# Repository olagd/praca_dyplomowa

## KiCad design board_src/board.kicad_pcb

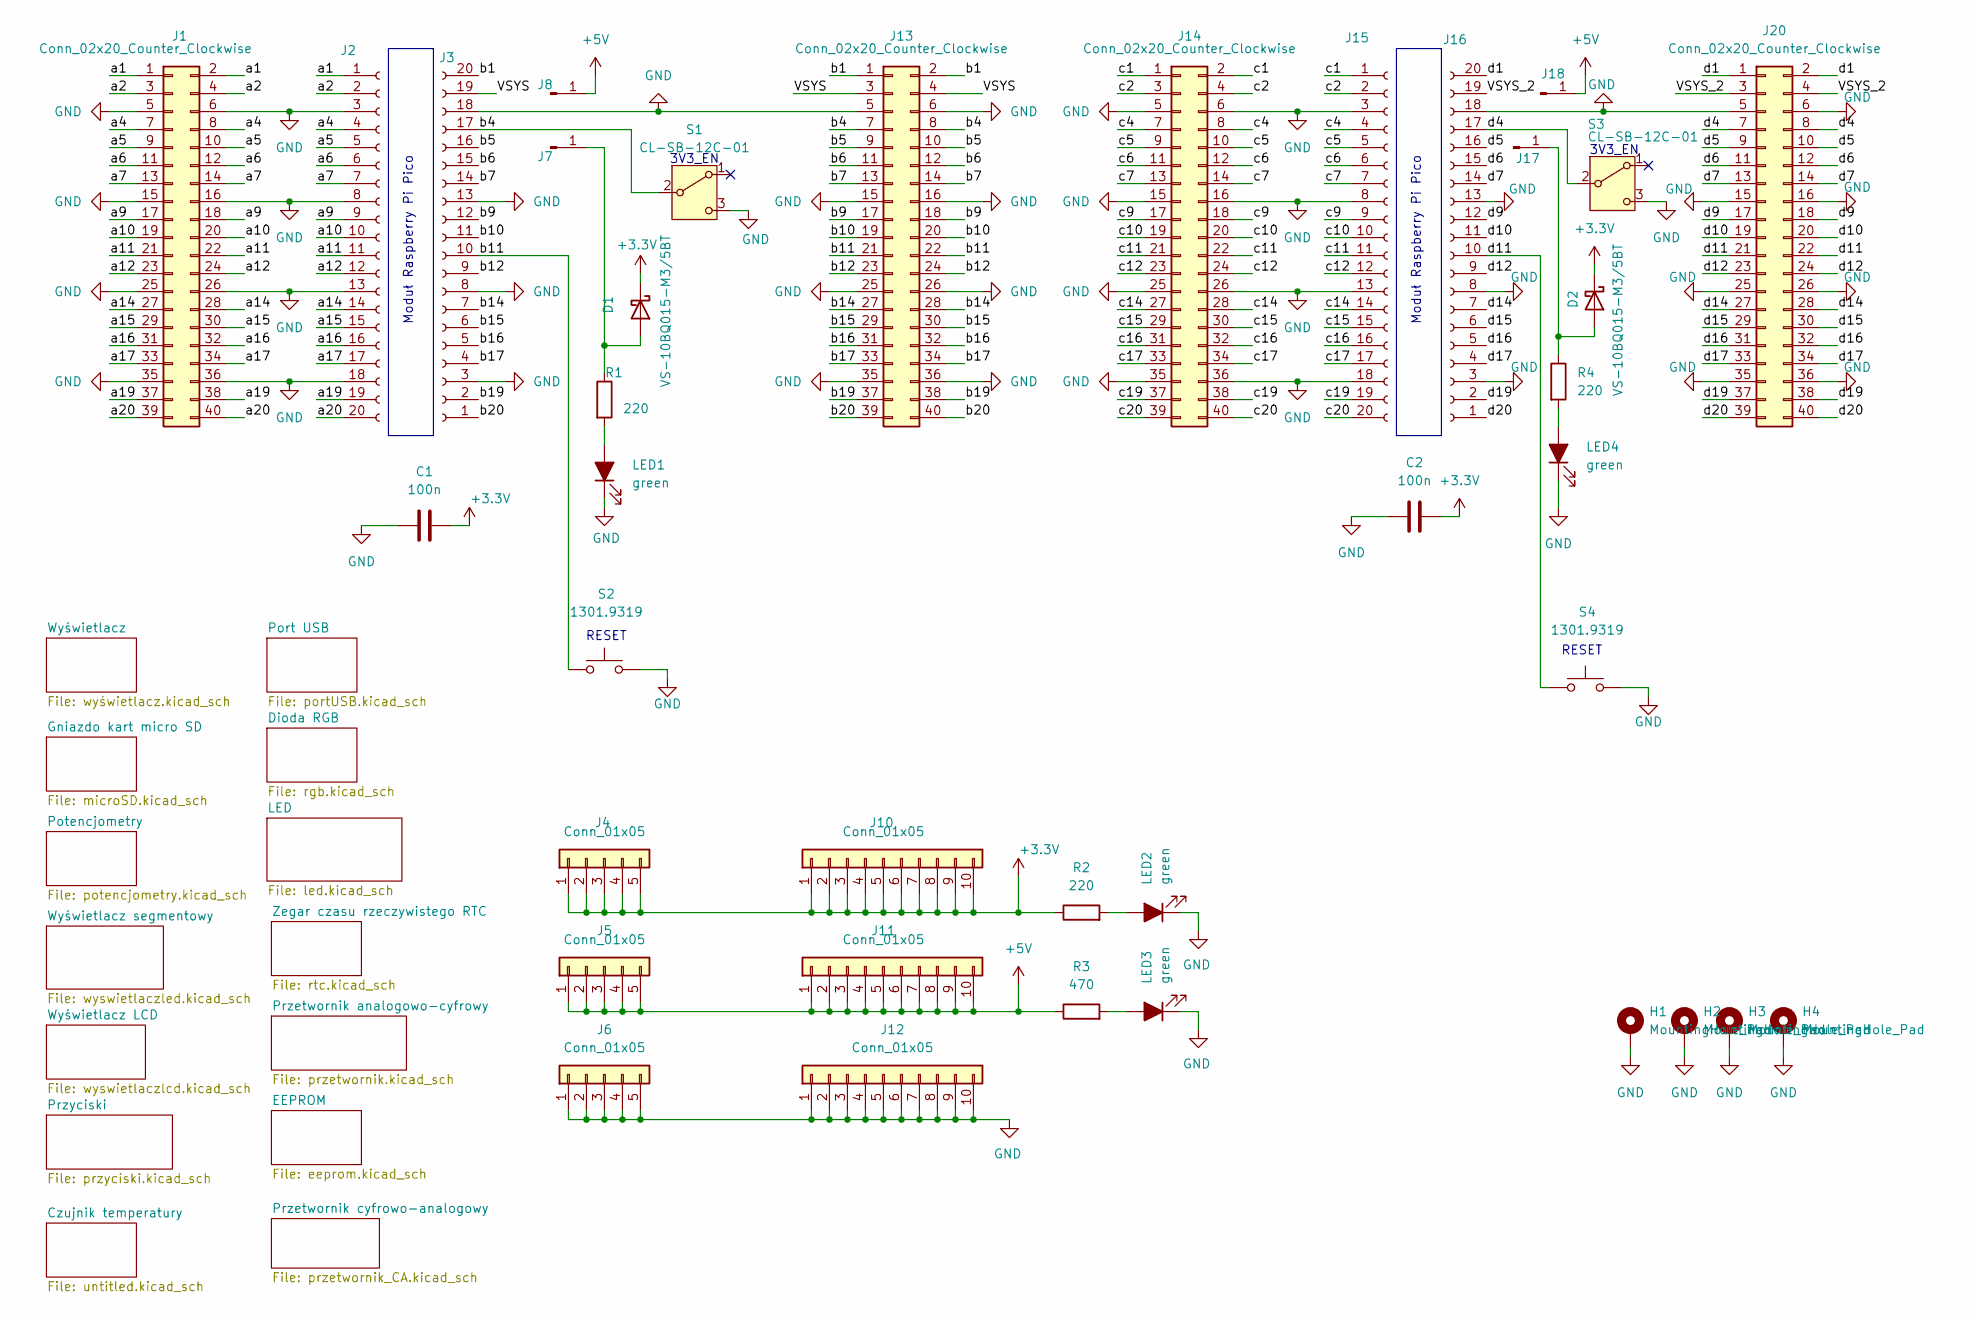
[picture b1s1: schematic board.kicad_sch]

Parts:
C1, C2: 100n; C_0603_1608Metric_Pad1.08x0.95mm_HandSolder
D1, D2: VS-10BQ015-M3/5BT; D_SMB_Handsoldering
H1, H2, H3, H4: MountingHole_Pad; MountingHole_3.2mm_M3_DIN965_Pad_TopBottom
J1, J13, J14, J20: Conn_02x20_Counter_Clockwise; PinHeader_2x20_P2.54mm_Vertical
J2, J3, J15, J16: Conn_01x20_Socket; PinSocket_1x20_P2.54mm_Vertical
J4, J5, J6, J10, J11, J12: Conn_01x05; PinHeader_1x05_P2.54mm_Vertical
J7, J8, J17, J18: Conn_01x01_Pin; PinHeader_1x01_P2.54mm_Vertical
LED1, LED2, LED3, LED4: green; LED_0603_1608Metric_Pad1.05x0.95mm_HandSolder; Manufacturer_Part_Number VLMTG1300-GS08
R1, R2, R4: 220; R_0603_1608Metric_Pad0.98x0.95mm_HandSolder
R3: 470; R_0603_1608Metric_Pad0.98x0.95mm_HandSolder
S1, S3: CL-SB-12C-01; JS102011CQN; Manufacturer_Part_Number CL-SB-12C-01
S2, S4: 1301.9319; SW_PUSH_6mm_H9.5mm; Manufacturer_Part_Number 1301.9319

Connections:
+3.3V: C1.2, C2.2, D1.1 (K), D2.1 (K), J4.1, J4.2, J4.3, J4.4, J4.5, J10.1, J10.2, J10.3, J10.4, J10.5, J10.6, J10.7, J10.8, J10.9, J10.10, R2.1; also elsewhere on the board
+5V: J5.1, J5.2, J5.3, J5.4, J5.5, J8.1, J11.1, J11.2, J11.3, J11.4, J11.5, J11.6, J11.7, J11.8, J11.9, J11.10, J18.1, R3.1; also elsewhere on the board
/VSYS: J3.19, J13.3, J13.4
/VSYS_2: J16.19, J20.3, J20.4
/a1: J1.1, J1.2, J2.1
/a2: J1.3, J1.4, J2.2
/a4: J1.7, J1.8, J2.4
/a5: J1.9, J1.10, J2.5
/a6: J1.11, J1.12, J2.6
/a7: J1.13, J1.14, J2.7
/a9: J1.17, J1.18, J2.9
/a10: J1.19, J1.20, J2.10
/a11: J1.21, J1.22, J2.11
/a12: J1.23, J1.24, J2.12
/a14: J1.27, J1.28, J2.14
/a15: J1.29, J1.30, J2.15
/a16: J1.31, J1.32, J2.16
/a17: J1.33, J1.34, J2.17
/a19: J1.37, J1.38, J2.19
/a20: J1.39, J1.40, J2.20
/b1: J3.20, J13.1, J13.2
/b4: J3.17, J13.7, J13.8, S1.2 (B)
/b5: J3.16, J13.9, J13.10
/b6: J3.15, J13.11, J13.12
/b7: J3.14, J13.13, J13.14
/b9: J3.12, J13.17, J13.18
/b10: J3.11, J13.19, J13.20
/b11: J3.10, J13.21, J13.22, S2.1
/b12: J3.9, J13.23, J13.24
/b14: J3.7, J13.27, J13.28
/b15: J3.6, J13.29, J13.30
/b16: J3.5, J13.31, J13.32
/b17: J3.4, J13.33, J13.34
/b19: J3.2, J13.37, J13.38
/b20: J3.1, J13.39, J13.40
/c1: J14.1, J14.2, J15.1
/c2: J14.3, J14.4, J15.2
/c4: J14.7, J14.8, J15.4
/c5: J14.9, J14.10, J15.5
/c6: J14.11, J14.12, J15.6
/c7: J14.13, J14.14, J15.7
/c9: J14.17, J14.18, J15.9
/c10: J14.19, J14.20, J15.10
/c11: J14.21, J14.22, J15.11
/c12: J14.23, J14.24, J15.12
/c14: J14.27, J14.28, J15.14
/c15: J14.29, J14.30, J15.15
/c16: J14.31, J14.32, J15.16
/c17: J14.33, J14.34, J15.17
/c19: J14.37, J14.38, J15.19
/c20: J14.39, J14.40, J15.20
/d1: J16.20, J20.1, J20.2
/d4: J16.17, J20.7, J20.8, S3.2 (B)
/d5: J16.16, J20.9, J20.10
/d6: J16.15, J20.11, J20.12
/d7: J16.14, J20.13, J20.14
/d9: J16.12, J20.17, J20.18
/d10: J16.11, J20.19, J20.20
/d11: J16.10, J20.21, J20.22, S4.1
/d12: J16.9, J20.23, J20.24
/d14: J16.7, J20.27, J20.28
/d15: J16.6, J20.29, J20.30
/d16: J16.5, J20.31, J20.32
/d17: J16.4, J20.33, J20.34
/d19: J16.2, J20.37, J20.38
/d20: J16.1, J20.39, J20.40
GND: C1.1, C2.1, H1.1, H2.1, H3.1, H4.1, J1.5, J1.6, J1.15, J1.16, J1.25, J1.26, J1.35, J1.36, J2.3, J2.8, J2.13, J2.18, J3.3, J3.8, J3.13, J3.18, J6.1, J6.2, J6.3, J6.4, J6.5, J12.1, J12.2, J12.3, J12.4, J12.5, J12.6, J12.7, J12.8, J12.9, J12.10, J13.5, J13.6, J13.15, J13.16, J13.25, J13.26, J13.35, J13.36, J14.5, J14.6, J14.15, J14.16, J14.25, J14.26, J14.35, J14.36, J15.3, J15.8, J15.13, J15.18, J16.3, J16.8, J16.13, J16.18, J20.5, J20.6, J20.15, J20.16, J20.25, J20.26, J20.35, J20.36, LED1.1 (K), LED2.1 (K), LED3.1 (K), LED4.1 (K), S1.3 (C), S2.2, S3.3 (C), S4.2; also elsewhere on the board
unnamed: D1.2 (A), J7.1, R1.1
unnamed: D2.2 (A), J17.1, R4.1
unnamed: LED1.2 (A), R1.2
unnamed: LED2.2 (A), R2.2
unnamed: LED3.2 (A), R3.2
unnamed: LED4.2 (A), R4.2

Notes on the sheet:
RESET
3V3_EN
Moduł Raspberry Pi Pico

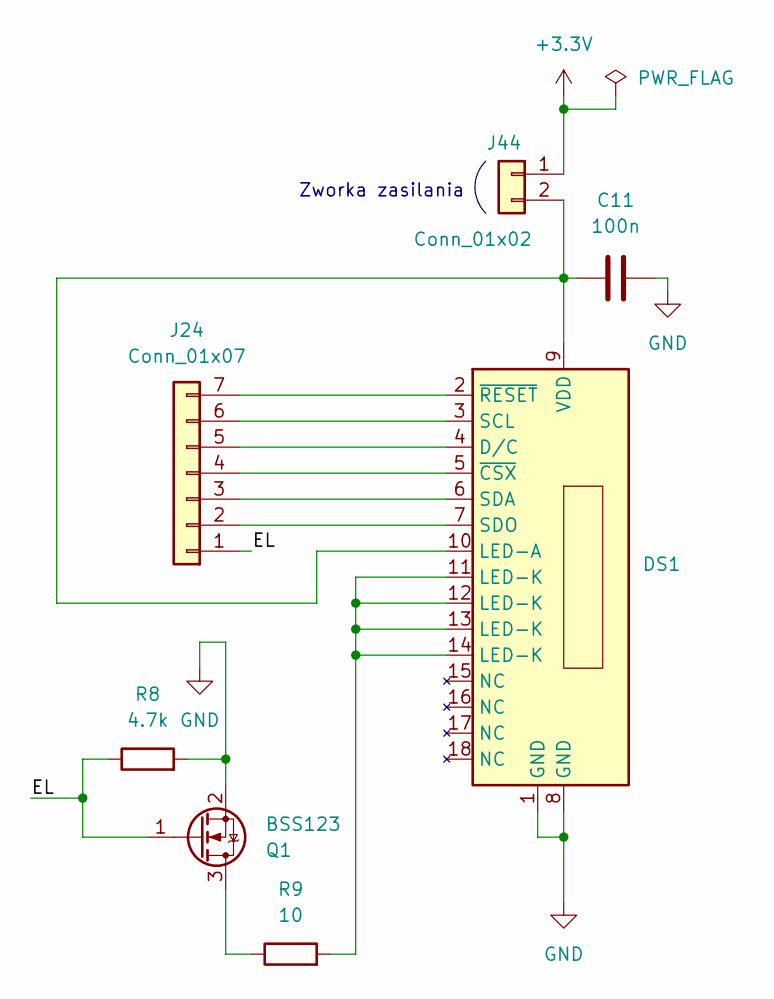
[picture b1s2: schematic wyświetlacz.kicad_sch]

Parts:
C11: 100n; C_0603_1608Metric_Pad1.08x0.95mm_HandSolder
DS1: HC28010-D; hc28010-d
J24: Conn_01x07; PinHeader_1x07_P2.54mm_Vertical
J44: Conn_01x02; PinHeader_1x02_P2.54mm_Vertical
Q1: BSS123; SOT-23_Handsoldering
R8: 4.7k; R_0603_1608Metric_Pad0.98x0.95mm_HandSolder
R9: 10; R_0603_1608Metric_Pad0.98x0.95mm_HandSolder

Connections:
+3.3V: J44.1; also elsewhere on the board
/Wyświetlacz/EL: J24.1, Q1.1 (G), R8.1
GND: C11.2, DS1.1 (GND), DS1.8 (GND), Q1.2 (S), R8.2; also elsewhere on the board
unnamed: DS1.4 (D/C), J24.5
unnamed: C11.1, DS1.9 (VDD), DS1.10 (LED-A), J44.2
unnamed: DS1.11 (LED-K), DS1.12 (LED-K), DS1.13 (LED-K), DS1.14 (LED-K), R9.2
unnamed: DS1.3 (SCL), J24.6
unnamed: DS1.6 (SDA), J24.3
unnamed: DS1.7 (SDO), J24.2
unnamed: DS1.5 (~CSX), J24.4
unnamed: DS1.2 (~RESET), J24.7
unnamed: Q1.3 (D), R9.1

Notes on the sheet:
Zworka zasilania

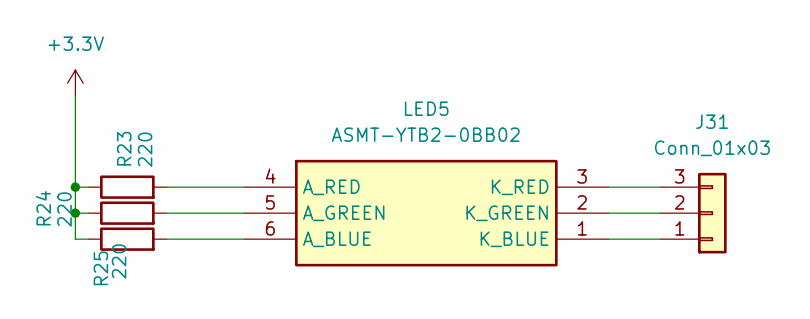
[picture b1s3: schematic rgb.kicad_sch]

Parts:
J31: Conn_01x03; PinHeader_1x03_P2.54mm_Vertical
LED5: ASMT-YTB2-0BB02; ASMT-YTC7-0AA02; Manufacturer_Part_Number ASMT-YTB2-0BB02
R23, R24, R25: 220; R_0603_1608Metric_Pad0.98x0.95mm_HandSolder

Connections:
+3.3V: R23.1, R24.1, R25.1; also elsewhere on the board
unnamed: J31.1, LED5.1 (K_BLUE)
unnamed: J31.2, LED5.2 (K_GREEN)
unnamed: J31.3, LED5.3 (K_RED)
unnamed: LED5.6 (A_BLUE), R25.2
unnamed: LED5.5 (A_GREEN), R24.2
unnamed: LED5.4 (A_RED), R23.2

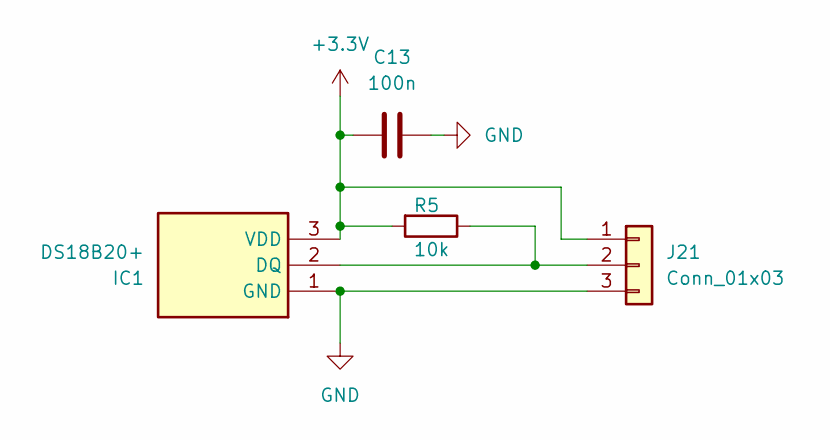
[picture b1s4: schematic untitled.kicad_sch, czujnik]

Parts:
C13: 100n; C_0603_1608Metric_Pad1.08x0.95mm_HandSolder
IC1: DS18B20+; TO-92L_Inline_Wide; Manufacturer_Part_Number DS18B20+
J21: Conn_01x03; PinHeader_1x03_P2.54mm_Vertical
R5: 10k; R_0603_1608Metric_Pad0.98x0.95mm_HandSolder

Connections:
+3.3V: C13.1, IC1.3 (VDD), J21.1, R5.2; also elsewhere on the board
GND: C13.2, IC1.1 (GND), J21.3; also elsewhere on the board
unnamed: IC1.2 (DQ), J21.2, R5.1

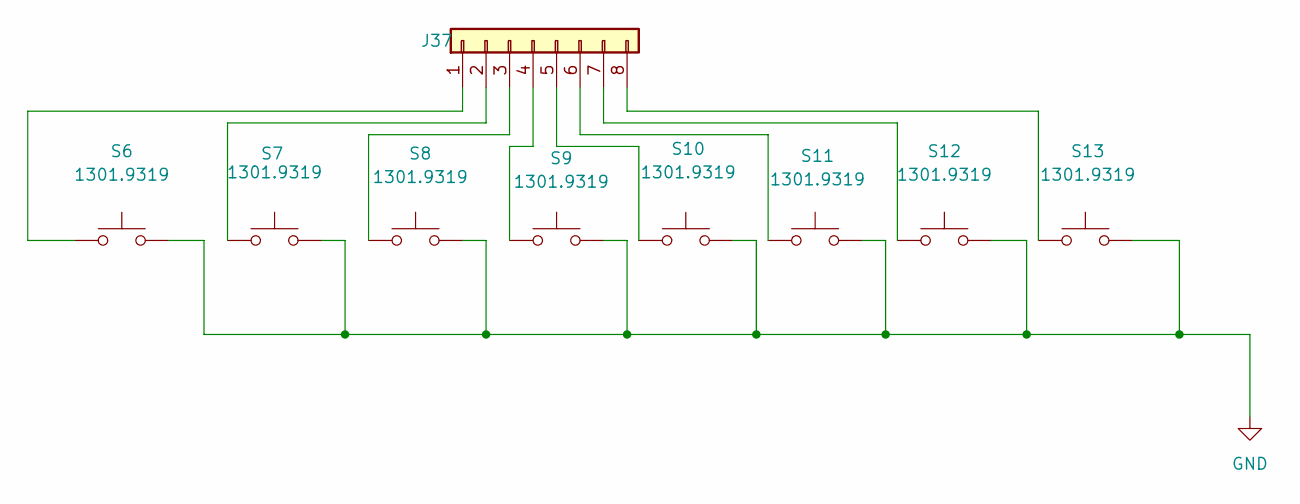
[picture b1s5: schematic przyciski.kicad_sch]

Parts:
J37: Conn_01x08; PinHeader_1x08_P2.54mm_Vertical
S6, S7, S8, S9, S10, S11, S12, S13: 1301.9319; SW_PUSH_6mm_H9.5mm; Manufacturer_Part_Number 1301.9319

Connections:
GND: S6.2, S7.2, S8.2, S9.2, S10.2, S11.2, S12.2, S13.2; also elsewhere on the board
unnamed: J37.1, S6.1
unnamed: J37.2, S7.1
unnamed: J37.3, S8.1
unnamed: J37.4, S9.1
unnamed: J37.5, S10.1
unnamed: J37.6, S11.1
unnamed: J37.7, S12.1
unnamed: J37.8, S13.1

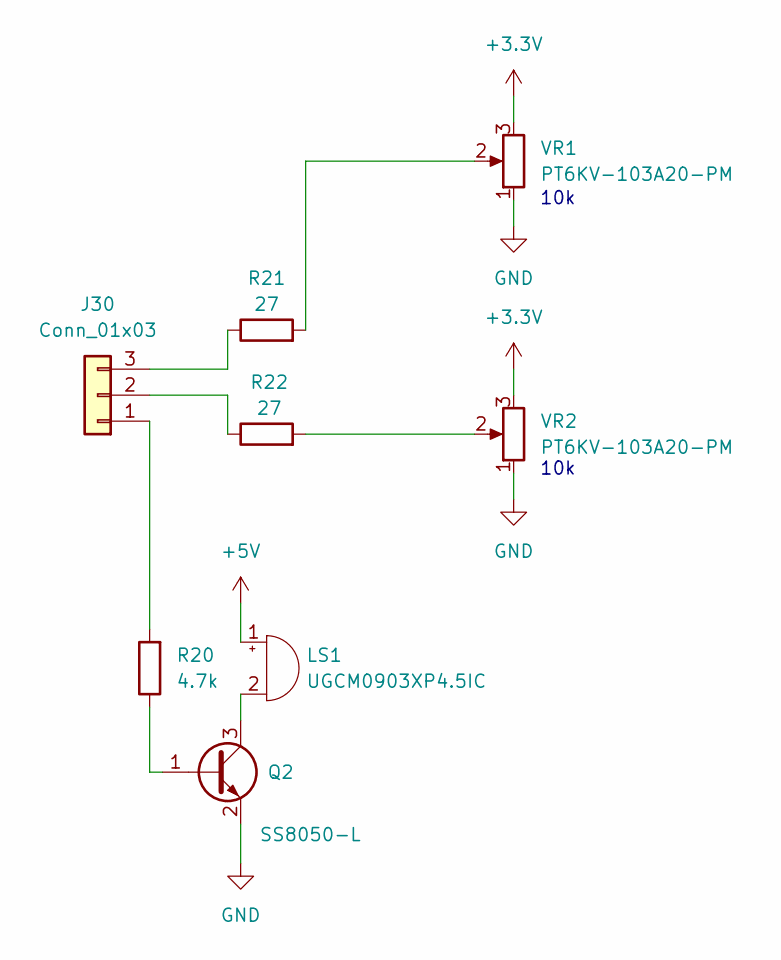
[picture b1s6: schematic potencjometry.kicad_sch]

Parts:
J30: Conn_01x03; PinHeader_1x03_P2.54mm_Vertical
LS1: UGCM0903XP4.5IC; BMT0905XH05; Manufacturer_Part_Number BMT0905XH05
Q2: SS8050-L; SOT-23_Handsoldering
R20: 4.7k; R_0603_1608Metric_Pad0.98x0.95mm_HandSolder
R21, R22: 27; R_0603_1608Metric_Pad0.98x0.95mm_HandSolder
VR1, VR2: PT6KV-103A20-PM; PT6KV251A2020; Mouser Part Number 531-PT6KV-251A2020

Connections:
+3.3V: VR1.3, VR2.3; also elsewhere on the board
+5V: LS1.1 (+); also elsewhere on the board
GND: Q2.2 (E), VR1.1, VR2.1; also elsewhere on the board
unnamed: J30.1, R20.2
unnamed: J30.2, R22.1
unnamed: J30.3, R21.1
unnamed: LS1.2 (-), Q2.3 (C)
unnamed: Q2.1 (B), R20.1
unnamed: R21.2, VR1.2
unnamed: R22.2, VR2.2

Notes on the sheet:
10k

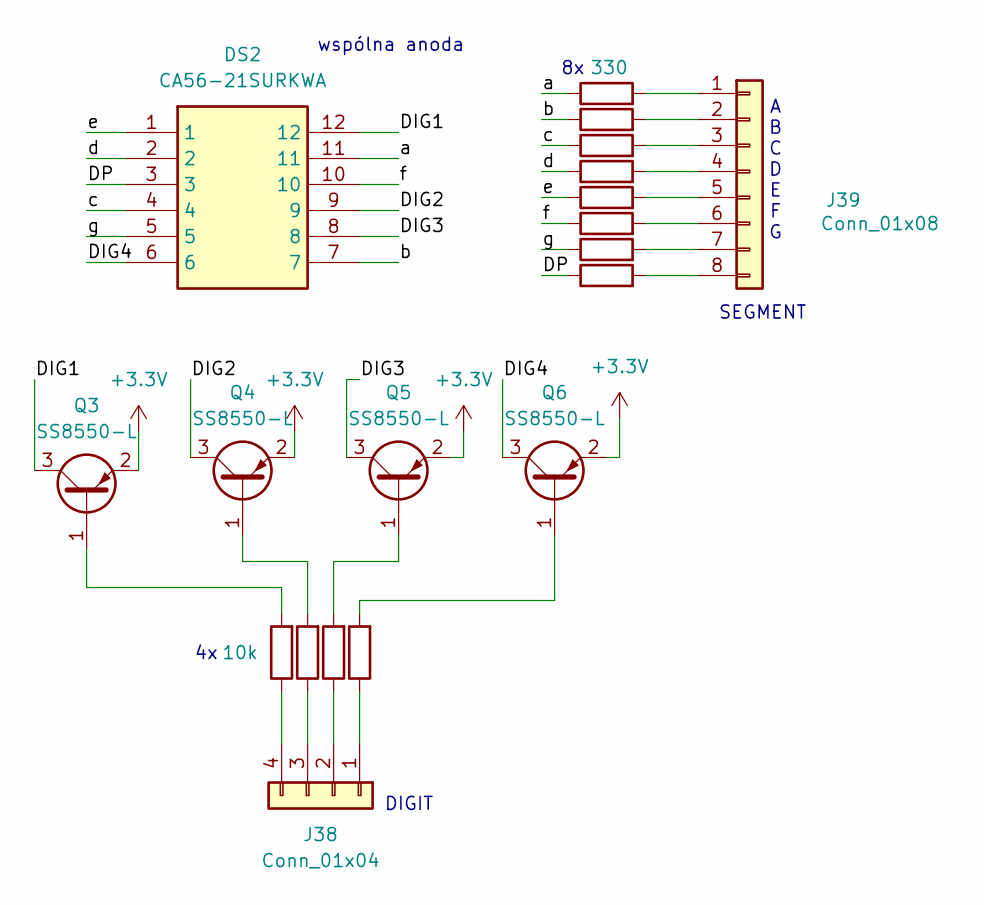
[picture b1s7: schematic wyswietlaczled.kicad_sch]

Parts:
DS2: CA56-21SURKWA; wyswietlacz7x4; Manufacturer_Part_Number CA56-21SURKWA
J38: Conn_01x04; PinHeader_1x04_P2.54mm_Vertical
J39: Conn_01x08; PinHeader_1x08_P2.54mm_Vertical
Q3, Q4, Q5, Q6: SS8550-L; SOT-23_Handsoldering
R39, R40, R41, R42: 10k; R_0603_1608Metric_Pad0.98x0.95mm_HandSolder
R43, R45, R46, R47, R48, R49, R50: 330; R_0603_1608Metric_Pad0.98x0.95mm_HandSolder
R44: 220; R_0603_1608Metric_Pad0.98x0.95mm_HandSolder

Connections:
+3.3V: Q3.2 (E), Q4.2 (E), Q5.2 (E), Q6.2 (E); also elsewhere on the board
/Wyświetlacz segmentowy/DIG1: DS2.12, Q3.3 (C)
/Wyświetlacz segmentowy/DIG2: DS2.9, Q4.3 (C)
/Wyświetlacz segmentowy/DIG3: DS2.8, Q5.3 (C)
/Wyświetlacz segmentowy/DIG4: DS2.6, Q6.3 (C)
/Wyświetlacz segmentowy/DP: DS2.3, R50.1
/Wyświetlacz segmentowy/a: DS2.11, R43.1
/Wyświetlacz segmentowy/b: DS2.7, R44.1
/Wyświetlacz segmentowy/c: DS2.4, R45.1
/Wyświetlacz segmentowy/d: DS2.2, R46.1
/Wyświetlacz segmentowy/e: DS2.1, R47.1
/Wyświetlacz segmentowy/f: DS2.10, R48.1
/Wyświetlacz segmentowy/g: DS2.5, R49.1
unnamed: J38.1, R42.1
unnamed: J38.2, R41.1
unnamed: J38.3, R40.1
unnamed: J38.4, R39.1
unnamed: J39.1, R43.2
unnamed: J39.2, R44.2
unnamed: J39.3, R45.2
unnamed: J39.4, R46.2
unnamed: J39.5, R47.2
unnamed: J39.6, R48.2
unnamed: J39.7, R49.2
unnamed: J39.8, R50.2
unnamed: Q3.1 (B), R39.2
unnamed: Q4.1 (B), R40.2
unnamed: Q5.1 (B), R41.2
unnamed: Q6.1 (B), R42.2

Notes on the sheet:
DIGIT
A B C D E F G
SEGMENT
wspólna anoda

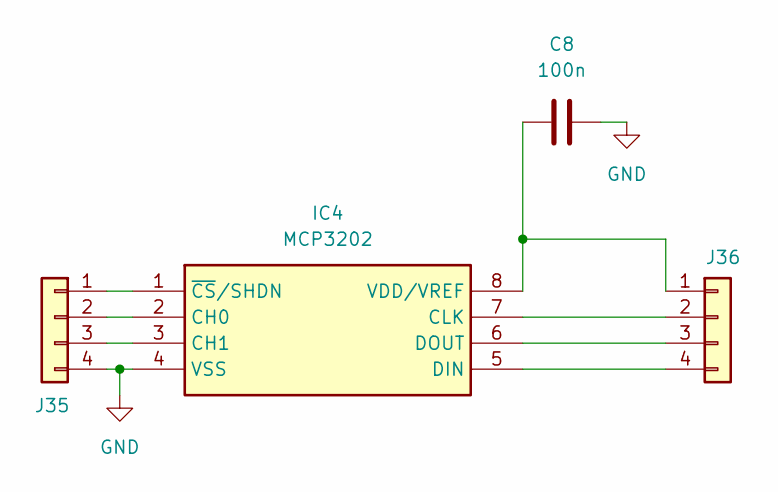
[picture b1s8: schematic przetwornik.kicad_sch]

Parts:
C8: 100n; C_0603_1608Metric_Pad1.08x0.95mm_HandSolder
IC4: MCP3202; DIP-8_W7.62mm_Socket_LongPads; Mouser Part Number 579-MCP3202-CI/MS
J35, J36: Conn_01x04; PinHeader_1x04_P2.54mm_Vertical

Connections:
GND: C8.2, IC4.4 (VSS), J35.4; also elsewhere on the board
unnamed: IC4.2 (CH0), J35.2
unnamed: IC4.3 (CH1), J35.3
unnamed: IC4.7 (CLK), J36.2
unnamed: IC4.5 (DIN), J36.4
unnamed: IC4.6 (DOUT), J36.3
unnamed: C8.1, IC4.8 (VDD/VREF), J36.1
unnamed: IC4.1 (~CS/SHDN), J35.1

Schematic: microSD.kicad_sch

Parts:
C6: 100n; C_0603_1608Metric_Pad1.08x0.95mm_HandSolder
J28: Conn_01x07; PinHeader_1x07_P2.54mm_Vertical
J29: 112J-TDAR-R01; 112JTDARR01; Manufacturer_Part_Number 112J-TDAR-R01
R13, R14, R15, R16, R17, R18, R19: 47k; R_0603_1608Metric_Pad0.98x0.95mm_HandSolder

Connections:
+3.3V: C6.2, J29.4 (VDD), R13.2, R14.2, R15.2, R16.2, R17.2, R18.2, R19.2; also elsewhere on the board
/Gniazdo kart micro SD/m1: J28.1, J29.1 (DAT2), R13.1
/Gniazdo kart micro SD/m2: J28.2, J29.2 (CD/DAT3), R14.1
/Gniazdo kart micro SD/m3: J28.3, J29.3 (CMD), R15.1
/Gniazdo kart micro SD/m4: J28.4, J29.5 (CLK), R16.1
/Gniazdo kart micro SD/m5: J28.5, J29.7 (DAT0), R17.1
/Gniazdo kart micro SD/m6: J28.6, J29.8 (DAT1), R18.1
/Gniazdo kart micro SD/m7: J28.7, J29.CD1 (CARD_DETECTION), R19.1
GND: C6.1, J29.6 (VSS), J29.G1 (GROUND), J29.MP1, J29.MP2, J29.MP3; also elsewhere on the board

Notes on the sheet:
7 x 47k rezystory podciągające

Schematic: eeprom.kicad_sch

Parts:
C3: 100n; C_0603_1608Metric_Pad1.08x0.95mm_HandSolder
IC2: M24C02-WMN6TP; SOIC-8_3.9x4.9mm_P1.27mm; Manufacturer_Part_Number M24C02-WMN6TP
J22, J23: Conn_01x02_Pin; PinHeader_1x02_P2.54mm_Vertical
R6, R7: 10k; R_0603_1608Metric_Pad0.98x0.95mm_HandSolder

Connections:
+3.3V: C3.1, IC2.8 (VCC), R6.2, R7.2; also elsewhere on the board
GND: C3.2, IC2.1 (E0), IC2.2 (E1), IC2.3 (E2), IC2.4 (VSS), IC2.7 (~WC), J22.1, J22.2; also elsewhere on the board
unnamed: IC2.6 (SCL), J23.2, R7.1
unnamed: IC2.5 (SDA), J23.1, R6.1

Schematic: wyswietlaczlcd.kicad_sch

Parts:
H5, H6, H7, H8: MountingHole; MountingHole_2.7mm_M2.5
J40: Conn_01x16_Socket; PinSocket_1x16_P2.54mm_Vertical
J41: Conn_02x07_Odd_Even; PinHeader_2x07_P2.54mm_Vertical
Q7: SS8050-L; SOT-23_Handsoldering
R51: 4.7k; R_0603_1608Metric_Pad0.98x0.95mm_HandSolder
R52: 50; R_0603_1608Metric_Pad0.98x0.95mm_HandSolder
RV1: 10K; PT6KV251A2020

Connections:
+3.3V: J41.4; also elsewhere on the board
+5V: J40.2, R52.1, RV1.1; also elsewhere on the board
/Wyświetlacz LCD/BL: J41.6, R51.1
/Wyświetlacz LCD/D0: J40.7, J41.8
/Wyświetlacz LCD/D1: J40.8, J41.10
/Wyświetlacz LCD/D2: J40.9, J41.12
/Wyświetlacz LCD/D3: J40.10, J41.14
/Wyświetlacz LCD/D4: J40.11, J41.7
/Wyświetlacz LCD/D5: J40.12, J41.9
/Wyświetlacz LCD/D6: J40.13, J41.11
/Wyświetlacz LCD/D7: J40.14, J41.13
/Wyświetlacz LCD/E: J40.6, J41.5
/Wyświetlacz LCD/RS: J40.4, J41.3
GND: J40.1, J40.5, J41.1, J41.2, Q7.2 (E), RV1.3; also elsewhere on the board
unnamed: J40.3, RV1.2
unnamed: J40.15, R52.2
unnamed: J40.16, Q7.3 (C)
unnamed: Q7.1 (B), R51.2

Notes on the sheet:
Dla bezpieczeństwa połączony z masą, by porty wyświetlacza były zawsze wejściowe i napięcie +5V nie pojawiło się na pinach GPIO Raspberry Pi Pico
R/W

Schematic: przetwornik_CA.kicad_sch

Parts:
C9, C10: 100n; C_0603_1608Metric_Pad1.08x0.95mm_HandSolder
IC5: MCP4921-E_P; DIP-8_W7.62mm_Socket_LongPads; Mouser Part Number 579-MCP4921-E/P
J42, J43: Conn_01x04; PinHeader_1x04_P2.54mm_Vertical

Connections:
GND: C9.2, C10.2, IC5.7 (VSS), J43.2; also elsewhere on the board
unnamed: IC5.3 (SCK), J42.3
unnamed: IC5.4 (SDI), J42.4
unnamed: C9.1, IC5.1 (VDD), J42.1
unnamed: IC5.8 (VOUT), J43.1
unnamed: C10.1, IC5.6 (VREF), J43.3
unnamed: IC5.2 (~CS), J42.2
unnamed: IC5.5 (~LDAC), J43.4

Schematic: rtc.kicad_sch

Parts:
C4: 10p; C_0603_1608Metric_Pad1.08x0.95mm_HandSolder
C5: 100n; C_0603_1608Metric_Pad1.08x0.95mm_HandSolder
D3, D4: VS-10BQ015-M3/5BT; D_SMB_Handsoldering
J25, J26: Conn_01x02_Pin; PinHeader_1x02_P2.54mm_Vertical
J27: Battery; PinHeader_1x02_P2.54mm_Vertical
R10: 47k; R_0603_1608Metric_Pad0.98x0.95mm_HandSolder
R11, R12: 10k; R_0603_1608Metric_Pad0.98x0.95mm_HandSolder
U1: PCF8563TS; TSSOP-8_3x3mm_P0.65mm
Y1: 32.768kHz; Crystal_AT310_D3.0mm_L10.0mm_Horizontal

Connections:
+3.3V: D4.2 (A), R10.1, R11.2, R12.2; also elsewhere on the board
/Zegar czasu rzeczywistego RTC/CLKOUT: J25.1, U1.7 (CLKO)
/Zegar czasu rzeczywistego RTC/INT: J25.2, R10.2, U1.3 (~INT)
GND: C4.1, C5.2, J27.1, U1.4 (VSS); also elsewhere on the board
unnamed: D3.2 (A), J27.2
unnamed: C5.1, D3.1 (K), D4.1 (K), U1.8 (VDD)
unnamed: J26.1, J26.3, R11.1, U1.6 (SCL)
unnamed: J26.2, J26.4, R12.1, U1.5 (SDA)
unnamed: C4.2, U1.1 (OSCI), Y1.1
unnamed: U1.2 (OSCO), Y1.2

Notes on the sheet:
Kondensator opcjonalny
Opcjonalna bateria podtrzymująca (1.5 .. 5) V
BAT+
BAT-

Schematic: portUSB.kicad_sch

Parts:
C7, C12: 100n; C_0603_1608Metric_Pad1.08x0.95mm_HandSolder
D5: VS-10BQ015-M3/5BT; D_SMB_Handsoldering
IC3: FT232RNL-TUBE; SOP65P780X200-28N; Manufacturer_Part_Number FT232RNL-TUBE
J32: Conn_02x05_Odd_Even; PinHeader_2x05_P2.54mm_Vertical
J33: USB_C_Receptacle_USB2.0_16P; USB_C_Receptacle_HRO_TYPE-C-31-M-12
LED6, LED8: green; LED_0603_1608Metric_Pad1.05x0.95mm_HandSolder; Manufacturer_Part_Number VLMTG1300-GS08
LED7: red; LED_0603_1608Metric_Pad1.05x0.95mm_HandSolder; Manufacturer_Part_Number LS Q976-NR-1
R26: 330; R_0603_1608Metric_Pad0.98x0.95mm_HandSolder
R27, R28: 5.1k; R_0603_1608Metric_Pad0.98x0.95mm_HandSolder
R29, R30: 220; R_0603_1608Metric_Pad0.98x0.95mm_HandSolder
S5: CL-SB-12C-01; JS102011CQN; Manufacturer_Part_Number CL-SB-12C-01

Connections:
+5V: C12.2, D5.1 (K), IC3.20 (VCC); also elsewhere on the board
/Port USB/3V3OUT: C7.1, IC3.4 (VCCIO), IC3.17 (3V3OUT), R29.1, R30.1
/Port USB/CB3: IC3.14 (CBUS3), J32.1
/Port USB/CB4: IC3.12 (CBUS4), J32.2
/Port USB/CTS: IC3.11 (CTS#), J32.3
/Port USB/DCD: IC3.10 (DCD#), J32.4
/Port USB/DSR: IC3.9 (DSR#), J32.5
/Port USB/DTR: IC3.2 (DTR#), J32.9
/Port USB/RI: IC3.6 (RI#), J32.6
/Port USB/RTS: IC3.3 (RTS#), J32.8
/Port USB/RXD: IC3.5 (RXD), J32.7
/Port USB/TXD: IC3.1 (TXD), J32.10
/Port USB/USBD+: IC3.15 (USBDP), J33.A6 (D+), J33.B6 (D+)
/Port USB/USBD-: IC3.16 (USBDM), J33.A7 (D-), J33.B7 (D-)
GND: C7.2, C12.1, IC3.7 (GND_1), IC3.18 (GND_2), IC3.21 (GND_3), IC3.25 (AGND), IC3.26 (TEST), J33.A1 (GND), J33.A12 (GND), J33.B1 (GND), J33.B12 (GND), J33.S1 (SHIELD), LED6.1 (K), R27.1, R28.1; also elsewhere on the board
unnamed: D5.2 (A), R26.1, S5.3 (C)
unnamed: IC3.23 (CBUS0), LED7.1 (K)
unnamed: IC3.22 (CBUS1), LED8.1 (K)
unnamed: J33.A5 (CC1), R28.2
unnamed: J33.B5 (CC2), R27.2
unnamed: LED6.2 (A), R26.2
unnamed: LED7.2 (A), R29.2
unnamed: LED8.2 (A), R30.2
unnamed: J33.A4 (VBUS), J33.A9 (VBUS), J33.B4 (VBUS), J33.B9 (VBUS), S5.2 (B)

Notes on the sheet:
+5V (VSYS)

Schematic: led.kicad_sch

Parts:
J34: Conn_01x08; PinHeader_1x08_P2.54mm_Vertical
LED9, LED11, LED13, LED15: red; LED_0603_1608Metric_Pad1.05x0.95mm_HandSolder; Manufacturer_Part_Number LS Q976-NR-1
LED10, LED12, LED14, LED16: green; LED_0603_1608Metric_Pad1.05x0.95mm_HandSolder; Manufacturer_Part_Number VLMTG1300-GS08
R31, R32, R33, R34, R35, R36, R37, R38: 220; R_0603_1608Metric_Pad0.98x0.95mm_HandSolder

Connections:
+3.3V: R31.1, R32.1, R33.1, R34.1, R35.1, R36.1, R37.1, R38.1; also elsewhere on the board
unnamed: J34.1, LED16.1 (K)
unnamed: J34.2, LED15.1 (K)
unnamed: J34.3, LED14.1 (K)
unnamed: J34.4, LED13.1 (K)
unnamed: J34.5, LED12.1 (K)
unnamed: J34.6, LED11.1 (K)
unnamed: J34.7, LED10.1 (K)
unnamed: J34.8, LED9.1 (K)
unnamed: LED9.2 (A), R31.2
unnamed: LED10.2 (A), R32.2
unnamed: LED11.2 (A), R33.2
unnamed: LED12.2 (A), R34.2
unnamed: LED13.2 (A), R35.2
unnamed: LED14.2 (A), R36.2
unnamed: LED15.2 (A), R37.2
unnamed: LED16.2 (A), R38.2

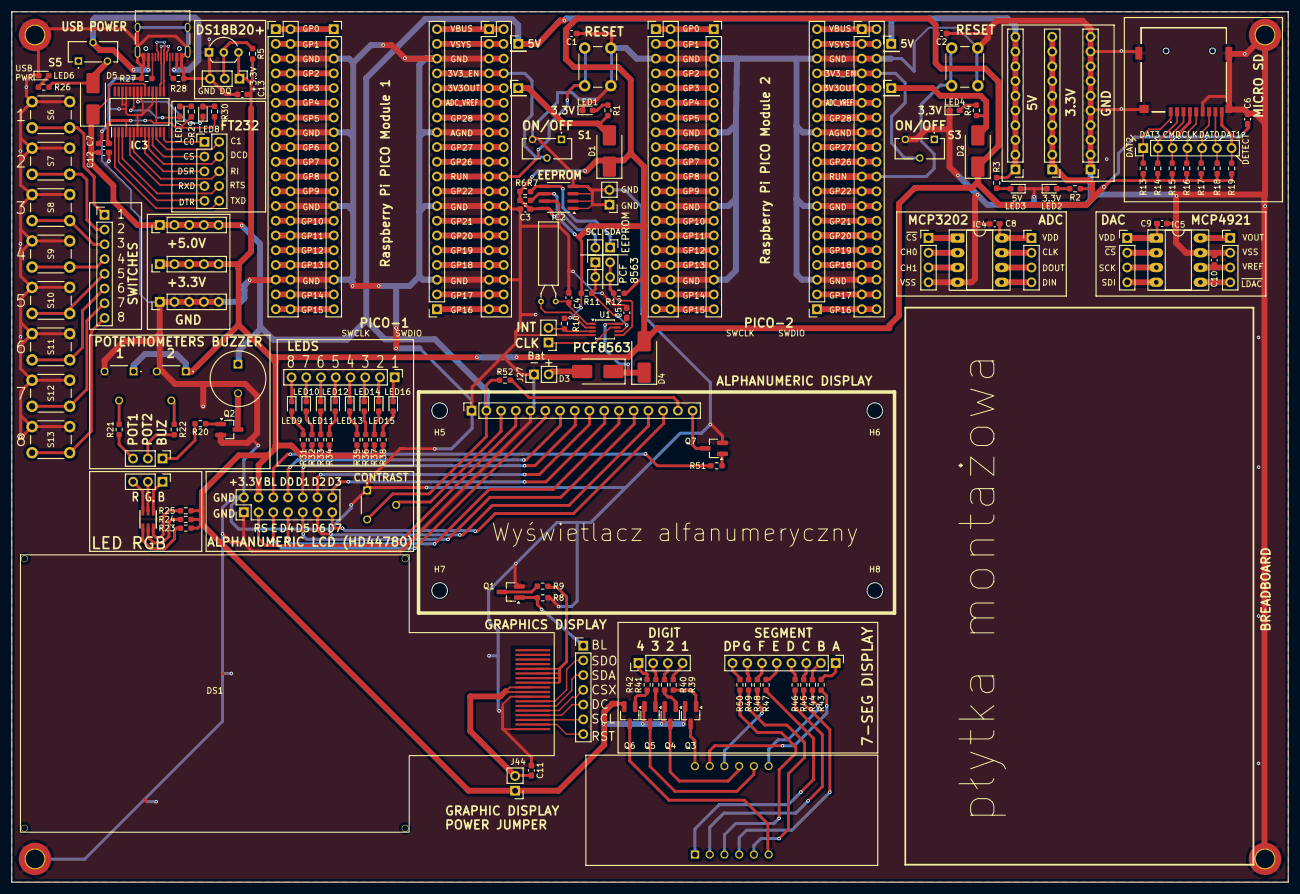
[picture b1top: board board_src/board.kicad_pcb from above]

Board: 2 copper layers, 220.0 x 150.0 mm, 169 parts (0 on the bottom side), 217 nets.

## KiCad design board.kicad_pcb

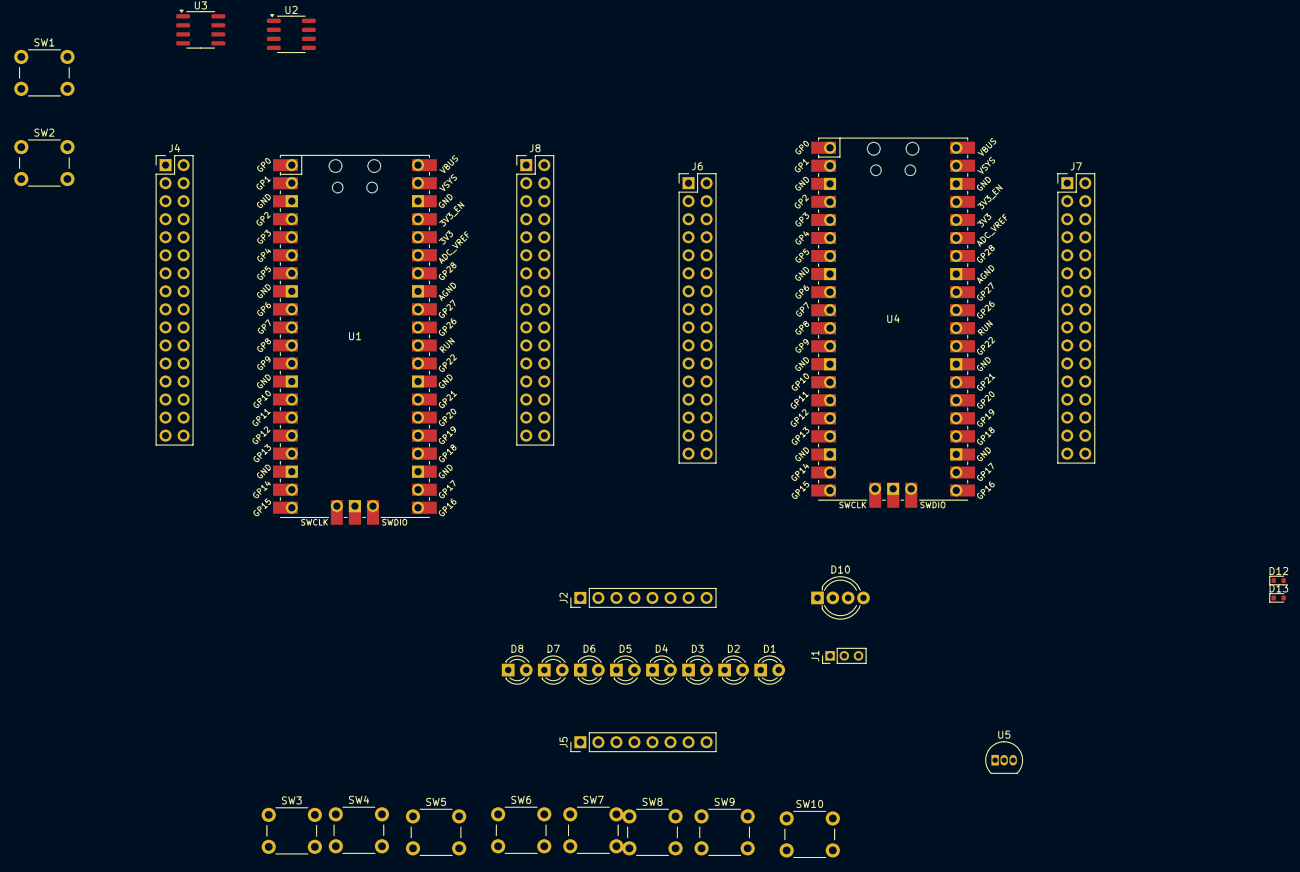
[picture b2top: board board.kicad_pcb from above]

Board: 2 copper layers, 33 parts (0 on the bottom side), 83 nets, no tracks yet.

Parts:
D1, D3, D5, D7: red; LED_D3.0mm_FlatTop
D2, D4, D6, D8: green; LED_D3.0mm_FlatTop
D10: LED; LED_D5.0mm-4_RGB_Wide_Pins
D12, D13: 1N4148WT; D_SOD-523
J1: Conn_01x03; PinHeader_1x03_P2.00mm_Vertical
J2, J5: Conn_01x08; PinHeader_1x08_P2.54mm_Vertical
J4, J6, J7, J8: Conn_02x16_Odd_Even; PinHeader_2x16_P2.54mm_Vertical
SW1, SW2: SW_Push; SW_PUSH_6mm
SW3, SW4, SW5, SW6, SW7, SW8, SW9, SW10: SW_PUSH_6mm
U1, U4: Pico; RPi_Pico_SMD_TH
U2: AT24CS04-SSHM; SOIC-8_3.9x4.9mm_P1.27mm
U3: PCF8563T; SOIC-8_3.9x4.9mm_P1.27mm
U5: DS18B20; TO-92_Inline

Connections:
+3.3V: D10.2 (A), U1.36 (3V3), U2.2 (A1), U2.8 (VCC), U3.8 (VDD), U4.36 (3V3), U5.3 (V_{DD})
/a1: J6.1, J6.2, U4.1 (GPIO0)
/a2: J6.3, J6.4, U4.2 (GPIO1)
/a3: J6.5, J6.6, U4.4 (GPIO2)
/a4: J6.7, J6.8, U4.5 (GPIO3)
/a5: J6.9, J6.10, U4.6 (GPIO4)
/a6: J6.11, J6.12, U4.7 (GPIO5)
/a7: J6.13, J6.14, U4.9 (GPIO6)
/a8: J6.15, J6.16, U4.10 (GPIO7)
/a9: J6.17, J6.18, U4.11 (GPIO8)
/a10: J6.19, J6.20, U4.12 (GPIO9)
/a11: J6.21, J6.22, U4.14 (GPIO10)
/a12: J6.23, J6.24, U4.15 (GPIO11)
/a13: J6.25, J6.26, U4.16 (GPIO12)
/a14: J6.27, J6.28, U4.17 (GPIO13)
/a15: J6.29, J6.30, U4.19 (GPIO14)
/a16: J6.31, J6.32, U4.20 (GPIO15)
/b1: J7.1, J7.2, U4.40 (VBUS)
/b2: J7.3, J7.4, U4.39 (VSYS)
/b3: J7.5, J7.6, U4.37 (3V3_EN)
/b4: J7.7, J7.8, U4.35 (ADC_VREF)
/b5: J7.9, J7.10, U4.34 (GPIO28_ADC2)
/b6: J7.11, J7.12, U4.33 (AGND)
/b7: J7.13, J7.14, J7.17, U4.32 (GPIO27_ADC1)
/b8: J7.15, J7.16, U4.31 (GPIO26_ADC0)
/b9: J7.18, U4.29 (GPIO22)
/b10: J7.19, J7.20, U4.27 (GPIO21)
/b11: J7.21, J7.22, U4.26 (GPIO20)
/b12: J7.23, J7.24, U4.25 (GPIO19)
/b13: J7.25, J7.26, U4.24 (GPIO18)
/b14: J7.27, J7.28, U4.22 (GPIO17)
/b15: J7.29, J7.30, U4.21 (GPIO16)
/c1: J4.1, J4.2, U1.1 (GPIO0)
/c2: J4.3, J4.4, U1.2 (GPIO1)
/c3: J4.5, J4.6, U1.4 (GPIO2)
/c4: J4.7, J4.8, U1.5 (GPIO3)
/c5: J4.9, J4.10, U1.6 (GPIO4)
/c6: J4.11, J4.12, U1.7 (GPIO5)
/c7: J4.13, J4.14, U1.9 (GPIO6)
/c8: J4.15, J4.16, U1.10 (GPIO7)
/c9: J4.17, J4.18, U1.11 (GPIO8)
/c10: J4.19, J4.20, U1.12 (GPIO9)
/c11: J4.21, J4.22, U1.14 (GPIO10)
/c12: J4.23, J4.24, U1.15 (GPIO11)
/c13: J4.25, J4.26, U1.16 (GPIO12)
/c14: J4.27, J4.28, U1.17 (GPIO13)
/c15: J4.29, J4.30, U1.19 (GPIO14)
/c16: J4.31, J4.32, U1.20 (GPIO15)
/d1: J8.1, J8.2, U1.40 (VBUS)
/d2: J8.3, J8.4, U1.39 (VSYS)
/d3: J8.5, J8.6, U1.37 (3V3_EN)
/d4: J8.7, J8.8, U1.35 (ADC_VREF)
/d5: J8.9, J8.10, U1.34 (GPIO28_ADC2)
/d6: J8.11, J8.12, U1.33 (AGND)
/d7: J8.13, J8.14, U1.32 (GPIO27_ADC1)
/d8: J8.15, J8.16, U1.31 (GPIO26_ADC0)
/d9: J8.17, J8.18, U1.29 (GPIO22)
/d10: J8.19, J8.20, U1.27 (GPIO21)
/d11: J8.21, J8.22, U1.26 (GPIO20)
/d12: J8.23, J8.24, U1.25 (GPIO19)
/d13: J8.25, J8.26, U1.24 (GPIO18)
/d14: J8.27, J8.28, U1.22 (GPIO17)
/d15: J8.29, J8.30, U1.21 (GPIO16)
GND: J7.31, J7.32, J8.31, J8.32, SW1.2, SW2.2, SW3.1, SW4.1, SW5.1, SW6.1, SW7.1, SW8.1, SW9.1, SW10.1, U1.3 (GND), U1.8 (GND), U1.13 (GND), U1.18 (GND), U1.23 (GND), U1.28 (GND), U1.38 (GND), U2.3 (A2), U2.4 (GND), U2.7 (WP), U3.4 (VSS), U4.3 (GND), U4.8 (GND), U4.13 (GND), U4.18 (GND), U4.23 (GND), U4.28 (GND), U4.38 (GND), U5.1 (GND)
unnamed: D1.1 (K), J2.8
unnamed: D2.1 (K), J2.7
unnamed: D3.1 (K), J2.6
unnamed: D4.1 (K), J2.5
unnamed: D5.1 (K), J2.4
unnamed: D6.1 (K), J2.3
unnamed: D7.1 (K), J2.2
unnamed: D8.1 (K), J2.1
unnamed: D12.1 (K), D13.1 (K)
unnamed: J5.1, SW3.2
unnamed: J5.2, SW4.2
unnamed: J5.3, SW5.2
unnamed: J5.4, SW6.2
unnamed: J5.5, SW7.2
unnamed: J5.6, SW8.2
unnamed: J5.7, SW9.2
unnamed: J5.8, SW10.2
unnamed: SW1.1, U1.30 (RUN)
unnamed: SW2.1, U4.30 (RUN)

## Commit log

2025-03-11 Wersja początkowa
2025-03-11 Wersja początkowa 9.0
2025-03-11 Dodano biblioteki z wyświetlaczem LCD
2025-03-14 wersja dodane arkusze hierarchiczne
2025-03-25 wersja dodane USB i port szeregowy
2025-03-25 wersja z przetwornikiem
2025-03-25 wersja uzupelnione footprinty
2025-03-31 wersja 3d
2025-04-01 uporzadkowane 3D
2025-04-03 wersja z wyswietlaczem LCD
2025-04-07 wersja z FT232RN
2025-04-29 Wersja ze sciezkami miedzianymi
2025-05-07 sciezki polaczen
2025-05-08 poprawione polaczenia diod i wartosci opornikow, aktualizacja niektorych elementow ze wzgledu na braki w magazynie
2025-05-15 dodany tranzystor BS123
2025-05-22 najnowsza wersja
2025-05-29 finalna wersja, naniesione poprawki
2025-06-14 Poprawki w schematach. Rozpoczęte korekty płytki
2025-06-16 Naniesione poprawki na projekcie płytki. Wersja końcowa
2025-06-16 Wprowadzono usprawnienia i poprawki. Wersja ostateczna, wysłana do JLCPCB.
